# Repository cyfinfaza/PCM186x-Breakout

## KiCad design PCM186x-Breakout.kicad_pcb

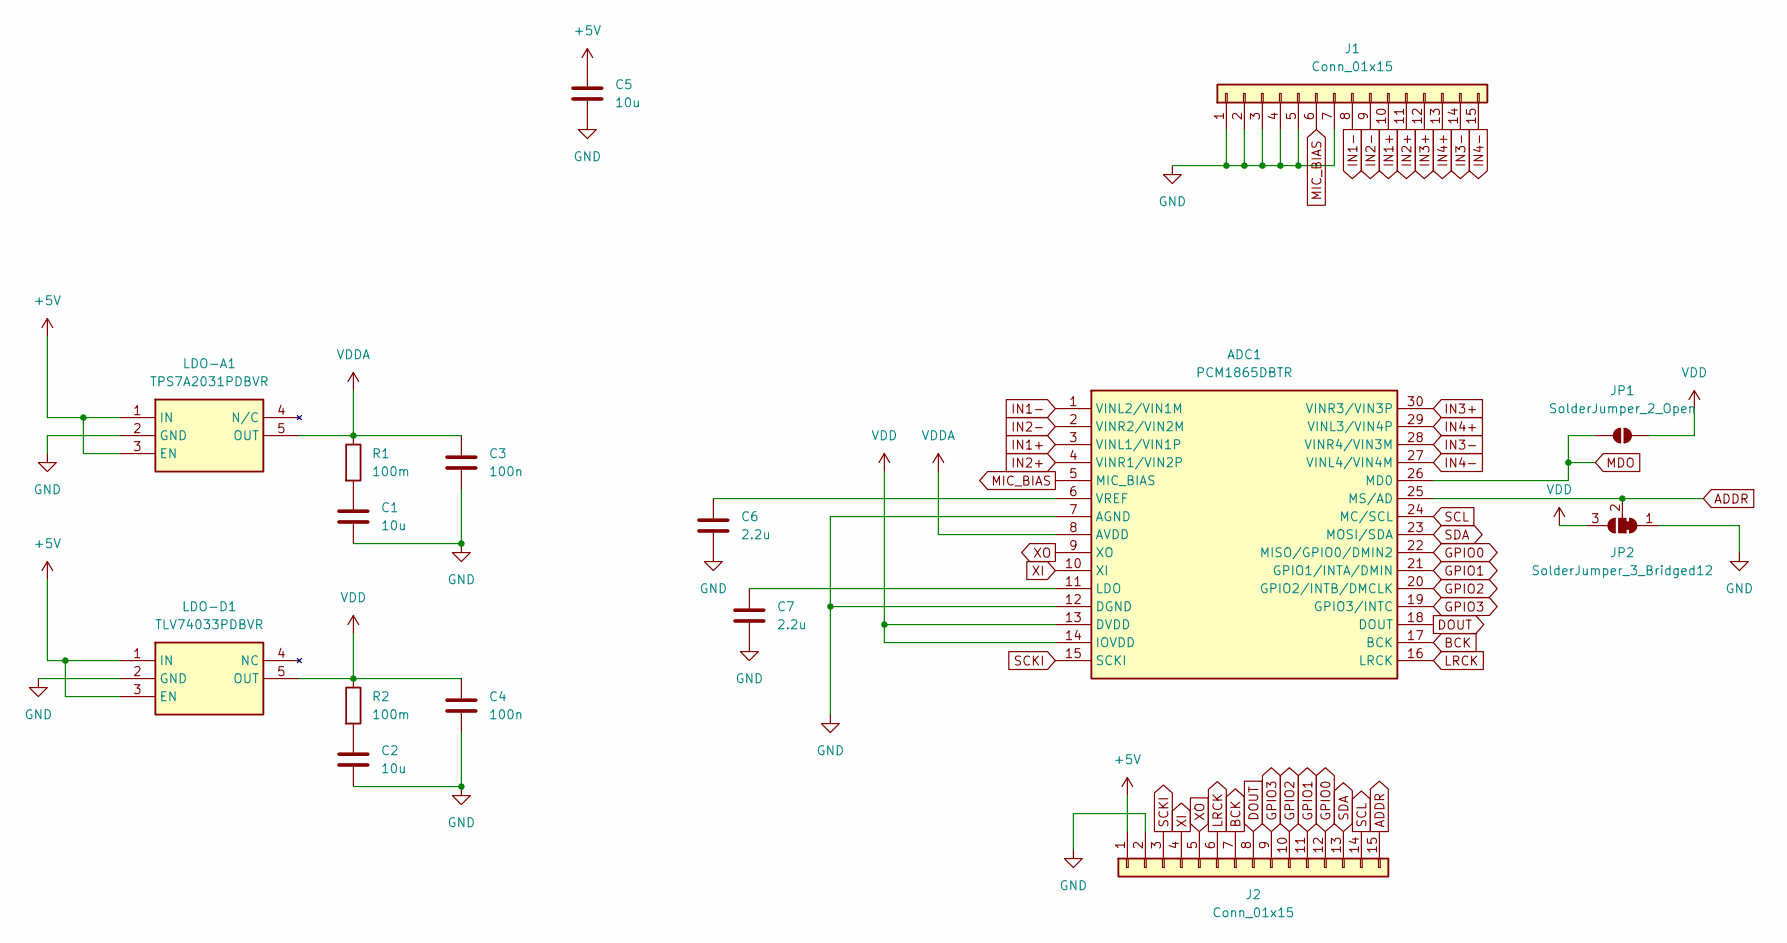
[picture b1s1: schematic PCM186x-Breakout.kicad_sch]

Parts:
ADC1: PCM1865DBTR; SOP50P640X120-30N; Mouser Part Number 595-PCM1865DBTR
C1, C2, C5: 10u; C_0805_2012Metric_Pad1.18x1.45mm_HandSolder
C3, C4: 100n; C_0603_1608Metric_Pad1.08x0.95mm_HandSolder
C6, C7: 2.2u; C_0603_1608Metric_Pad1.08x0.95mm_HandSolder
J1, J2: Conn_01x15; PinHeader_1x15_P2.54mm_Vertical
JP1: SolderJumper_2_Open; SolderJumper-2_P1.3mm_Open_RoundedPad1.0x1.5mm
JP2: SolderJumper_3_Bridged12; SolderJumper-3_P1.3mm_Bridged12_RoundedPad1.0x1.5mm
LDO-A1: TPS7A2031PDBVR; SOT95P280X145-5N; Mouser Part Number 595-TPS7A2031PDBVR
LDO-D1: TLV74033PDBVR; SOT95P280X145-5N; Mouser Part Number 595-TLV74033PDBVR
R1, R2: 100m; R_0603_1608Metric_Pad0.98x0.95mm_HandSolder

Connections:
+5V: C5.1, J2.1, LDO-A1.1 (IN), LDO-A1.3 (EN), LDO-D1.1 (IN), LDO-D1.3 (EN)
ADDR: ADC1.25 (MS/AD), J2.15, JP2.2 (C)
BCK: ADC1.17 (BCK), J2.7
DOUT: ADC1.18 (DOUT), J2.8
GND: ADC1.7 (AGND), ADC1.12 (DGND), C1.2, C2.2, C3.2, C4.2, C5.2, C6.2, C7.2, J1.1, J1.2, J1.3, J1.4, J1.5, J1.7, J2.2, JP2.1 (A), LDO-A1.2 (GND), LDO-D1.2 (GND)
GPIO0: ADC1.22 (MISO/GPIO0/DMIN2), J2.12
GPIO1: ADC1.21 (GPIO1/INTA/DMIN), J2.11
GPIO2: ADC1.20 (GPIO2/INTB/DMCLK), J2.10
GPIO3: ADC1.19 (GPIO3/INTC), J2.9
IN1+: ADC1.3 (VINL1/VIN1P), J1.10
IN1-: ADC1.1 (VINL2/VIN1M), J1.8
IN2+: ADC1.4 (VINR1/VIN2P), J1.11
IN2-: ADC1.2 (VINR2/VIN2M), J1.9
IN3+: ADC1.30 (VINR3/VIN3P), J1.12
IN3-: ADC1.28 (VINR4/VIN3M), J1.14
IN4+: ADC1.29 (VINL3/VIN4P), J1.13
IN4-: ADC1.27 (VINL4/VIN4M), J1.15
LRCK: ADC1.16 (LRCK), J2.6
MDO: ADC1.26 (MD0), JP1.1 (A)
MIC_BIAS: ADC1.5 (MIC_BIAS), J1.6
unnamed: ADC1.11 (LDO), C7.1
unnamed: ADC1.6 (VREF), C6.1
unnamed: C1.1, R1.2
unnamed: C2.1, R2.2
SCKI: ADC1.15 (SCKI), J2.3
SCL: ADC1.24 (MC/SCL), J2.14
SDA: ADC1.23 (MOSI/SDA), J2.13
VDD: ADC1.13 (DVDD), ADC1.14 (IOVDD), C4.1, JP1.2 (B), JP2.3 (B), LDO-D1.5 (OUT), R2.1
VDDA: ADC1.8 (AVDD), C3.1, LDO-A1.5 (OUT), R1.1
XI: ADC1.10 (XI), J2.4
XO: ADC1.9 (XO), J2.5

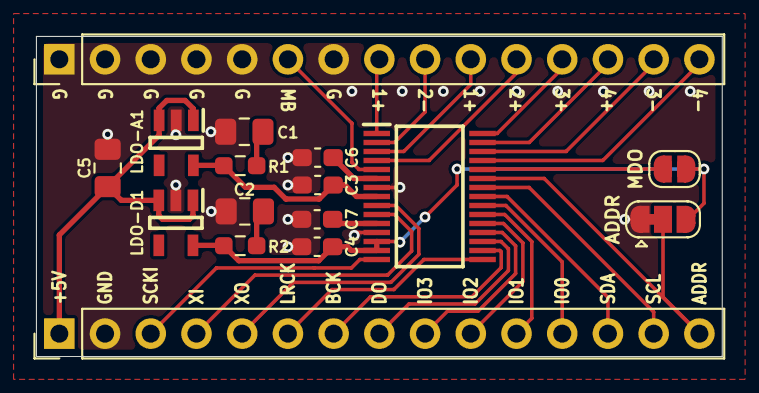
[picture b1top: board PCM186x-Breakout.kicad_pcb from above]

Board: 2 copper layers, 38.1 x 17.8 mm, 16 parts (0 on the bottom side), 31 nets.

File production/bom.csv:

Designator,Footprint,Quantity,Value,LCSC Part #
ADC1,SOP50P640X120-30N,1,PCM1865DBTR,
"C1, C2, C5",0805,3,10u,
"C3, C4",0603,2,100n,
"C6, C7",0603,2,2.2u,
"J1, J2",PinHeader_1x15_P2.54mm_Vertical,2,Conn_01x15,
LDO-A1,SOT95P280X145-5N,1,TPS7A2031PDBVR,
LDO-D1,SOT95P280X145-5N,1,TLV74033PDBVR,
"R1, R2",0603,2,100m,

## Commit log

2026-03-22 addr pad, kicad 10, routing, silkscreen
2026-03-29 make unused pins ground
2026-03-30 r0 final
2026-04-01 specify 3.3 V version of analog LDO instead of 3.1 V version
